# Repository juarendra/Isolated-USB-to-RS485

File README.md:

# Industrial USB to RS485 Adapter

USB Type-C to isolated half-duplex RS485 interface for Modbus RTU and other UART-based industrial networks.

## Product Summary

This board converts a USB serial connection into an electrically isolated RS485 bus. It is suitable for connecting a computer, single-board computer, or industrial controller to RS485/Modbus RTU equipment.

```text
USB Type-C -> FT231XS UART -> ADuM1201 isolation -> MAX485 -> RS485 A/B
```

The design files are provided for evaluation, manufacturing, and integration. Read the limitations and validation notes before using the board in a safety-critical or compliance-regulated product.

## Features

- USB Type-C USB 2.0 connection
- FTDI FT231XS USB-to-UART bridge
- 3.3 V UART I/O configuration
- Isolated UART data path using ADuM1201ARZ
- Isolated 5 V supply using IL0505S
- MAX485 half-duplex RS485 transceiver
- RS485 A, B, and isolated ground connector
- Selectable RS485 termination and bias networks
- RS485 transient protection using SM712, TBU, and TISP devices
- TX, RX, and power status indicators
- Resettable USB input protection
- Separate isolated 5 V output connector
- Eagle schematic, board, libraries, Gerber archive, 3D model, and enclosure files

## Quick Start

1. Connect the board to a host computer using a USB Type-C data cable.
2. Install the FTDI VCP driver if the operating system does not install it automatically.
3. Identify the new serial port.
4. Connect RS485 `A`, `B`, and optionally `GNDA` to the target equipment.
5. Configure the host application for the target baud rate, parity, stop bits, and protocol.
6. Enable termination only when this adapter is at a physical end of the RS485 bus.
7. Enable bias only when this adapter is the designated bias point for the bus.

## Connector Pinout

See the visual pinout: [`DOC/HARDWARE/Pinout.png`](DOC/HARDWARE/Pinout.png).

| Connector | Pin | Function |
|---|---:|---|
| RS485 | 1 | `GNDA` / isolated ground |
| RS485 | 2 | `B` |
| RS485 | 3 | `A` |
| POWER | 1 | `GNDA` |
| POWER | 2 | `VCC`, isolated 5 V |
| POWER | 3 | `VCC`, isolated 5 V |

Confirm connector orientation against the silkscreen and pinout image before wiring.

## Design Files

| Resource | Location |
|---|---|
| Schematic PDF | [`PDF/Schematic.pdf`](PDF/Schematic.pdf) |
| Eagle schematic | [`PCB-EAGLE/IndustrialUSBtoModbus.sch`](PCB-EAGLE/IndustrialUSBtoModbus.sch) |
| Eagle board | [`PCB-EAGLE/IndustrialUSBtoModbus.brd`](PCB-EAGLE/IndustrialUSBtoModbus.brd) |
| Manufacturing Gerbers | [`CAD-CAM/Gerber.zip`](CAD-CAM/Gerber.zip) |
| Production PCB | [`PCB-EAGLE/IndustrialUSBtoModbus_Production.brd`](PCB-EAGLE/IndustrialUSBtoModbus_Production.brd) |
| Production Gerbers | [`CAD-CAM/Gerber_Production.zip`](CAD-CAM/Gerber_Production.zip) |
| Production CAM job | [`CAD-CAM/IndustrialUSBtoModbus v2.cam`](CAD-CAM/IndustrialUSBtoModbus%20v2.cam) |
| Board dimensions | [`DOC/Dimension.pdf`](DOC/Dimension.pdf) |
| STEP model | [`3D/IndustrialUSBtoModbus.step`](3D/IndustrialUSBtoModbus.step) |
| Enclosure models | [`3D/Case/`](3D/Case/) |
| Custom Eagle libraries | [`PCB-EAGLE/lib/`](PCB-EAGLE/lib/) |

Detailed documentation is in [`docs/`](docs/).

For manufacturing, use the files marked **Production**. The production Gerber archive contains Gerber, drill, solder-paste, pick-and-place, job, and ODB++ outputs generated from the production PCB revision.

## Important Limitations

- This is a half-duplex RS485 hardware interface; it does not implement Modbus protocol in hardware.
- RS485 termination, bias values, isolation spacing, and protection ratings require system-level verification.
- Cable length, baud rate, node count, and bus topology depend on the transceiver, cable, and installation.
- Custom FTDI VID/PID programming requires valid ownership/licensing and separate production configuration.

## Buyer Information

Before purchasing or manufacturing, review:

- [`docs/BUYER-GUIDE.md`](docs/BUYER-GUIDE.md) for compatibility and ordering checks
- [`docs/HARDWARE.md`](docs/HARDWARE.md) for circuit behavior and configuration
- [`docs/VALIDATION.md`](docs/VALIDATION.md) for required production tests
- [`docs/FTDI-PROGRAMMING.md`](docs/FTDI-PROGRAMMING.md) for FT231XS production programming
- [`docs/FILES.md`](docs/FILES.md) for the complete repository map

## License

No license is currently declared. Contact the repository owner for permission to manufacture, modify, or redistribute this design.

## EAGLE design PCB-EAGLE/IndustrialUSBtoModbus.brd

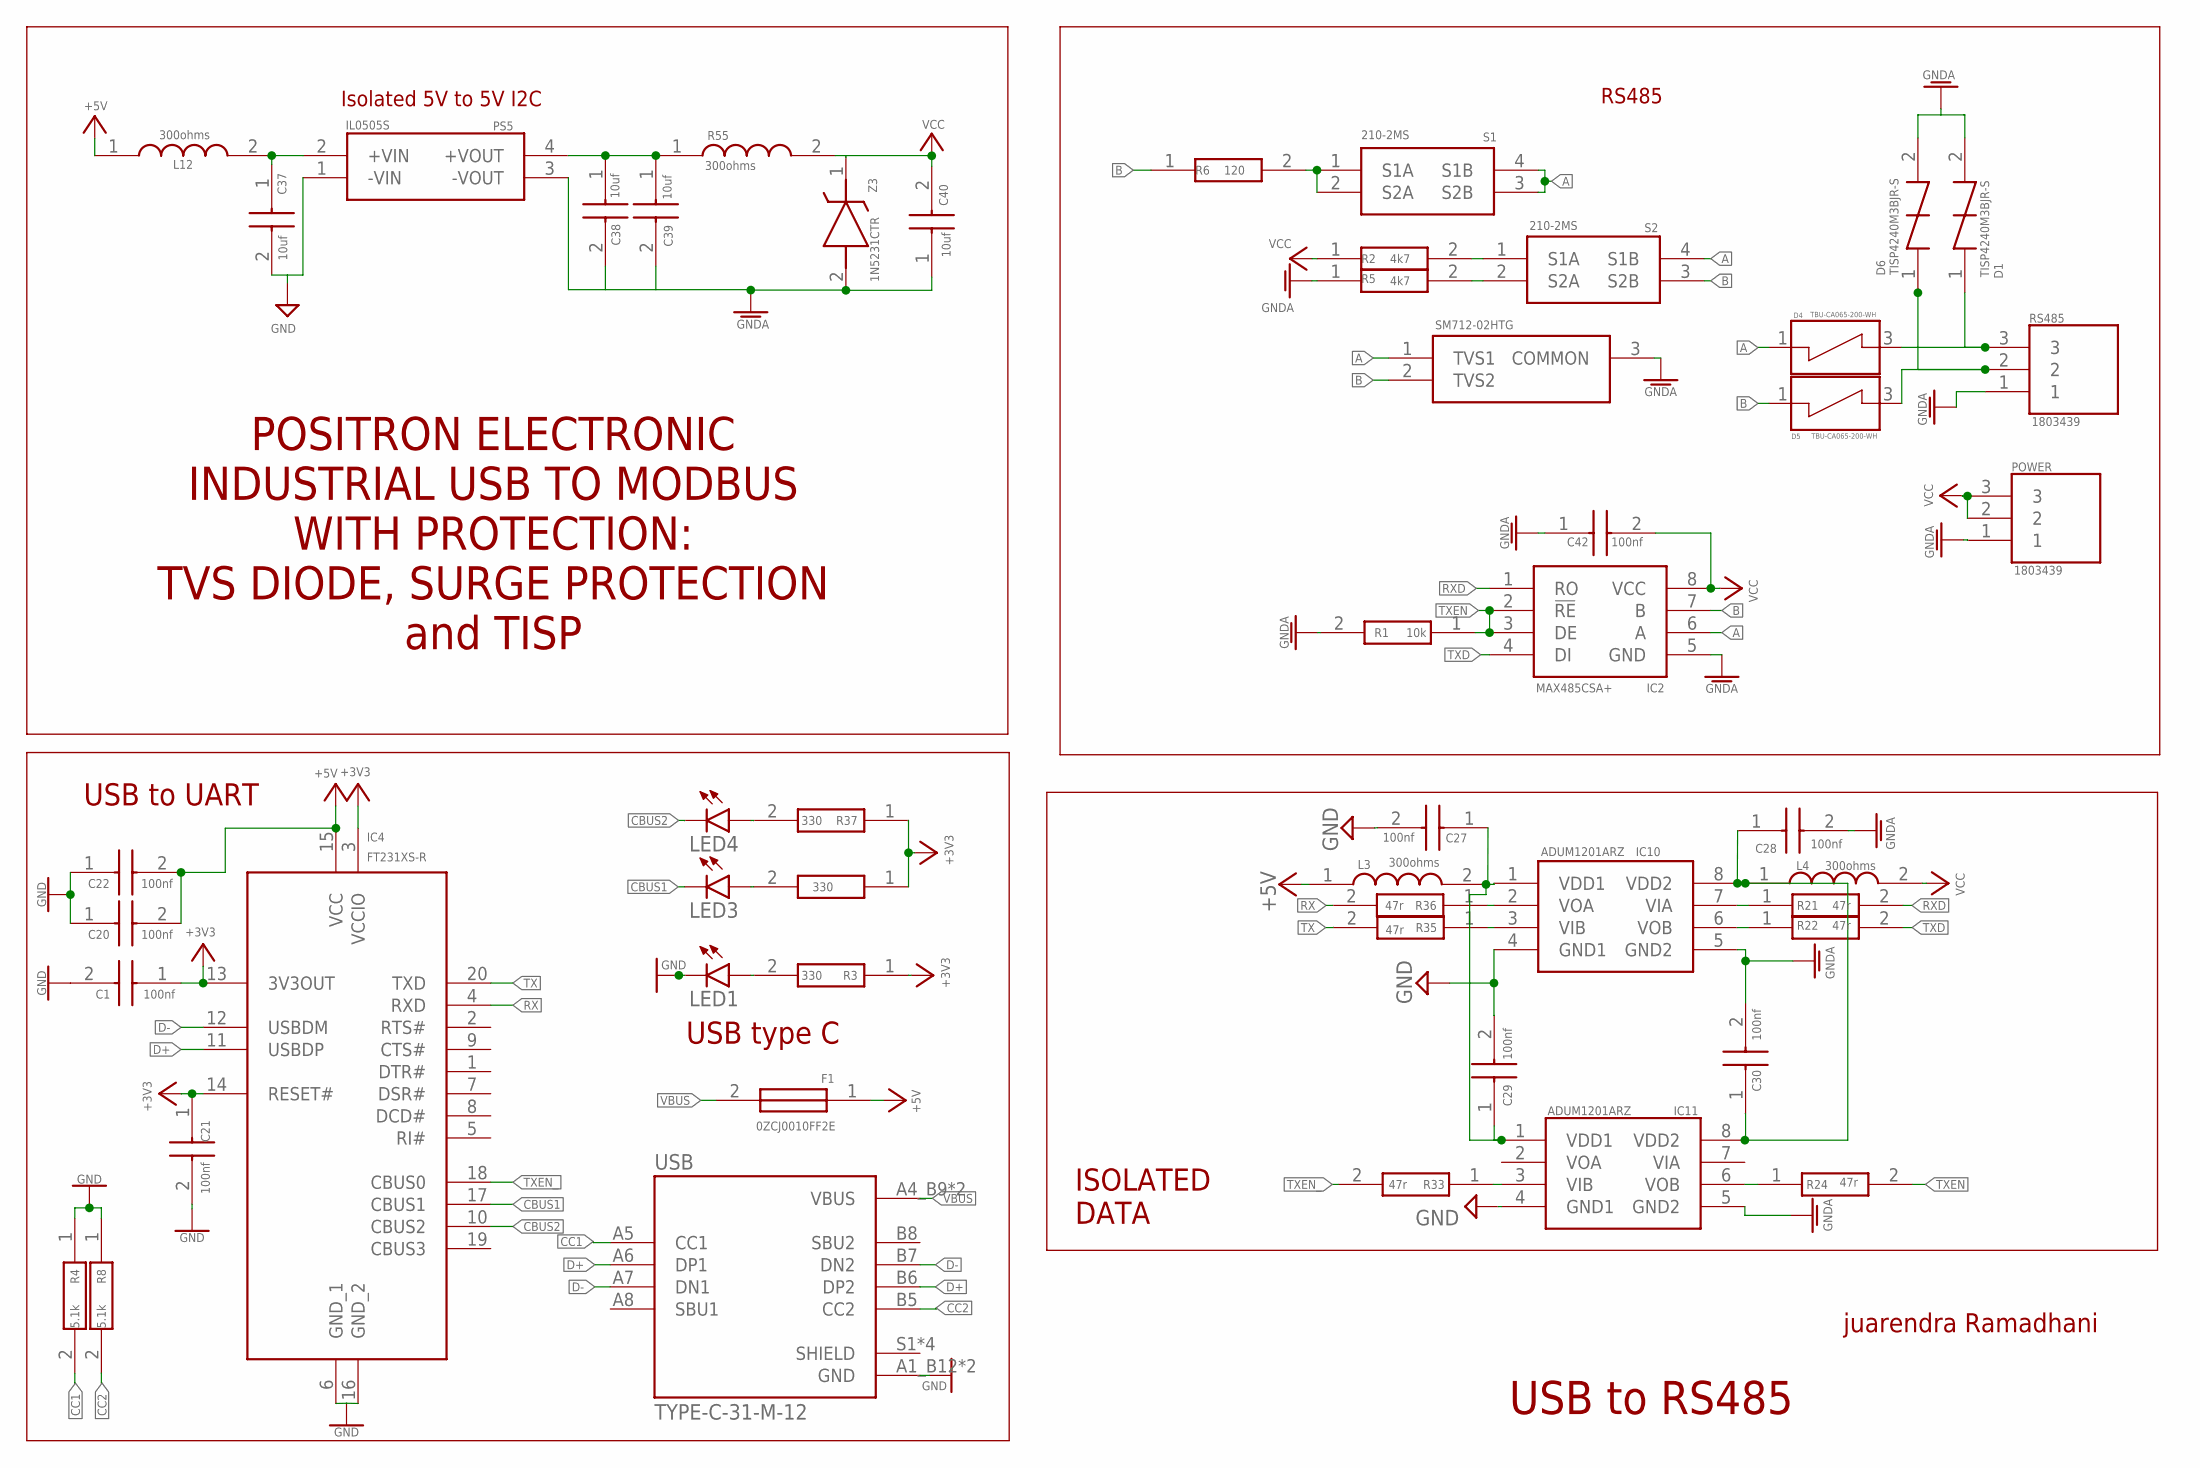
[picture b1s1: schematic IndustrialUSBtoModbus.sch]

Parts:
C1, C20, C21, C22, C27, C28, C29, C30, C42: 100nf; CAPC1608X87N
C37, C38, C39, C40: 10uf; CAPC3216X170N
D1, D6: TISP4240M3BJR-S; TISP4240M3BJRS
D2: SM712-02HTG; SOT95P237X111-3N
D4, D5: TBU-CA065-200-WH; DIOC650X400X100N
F1: 0ZCJ0010FF2E; FUSC3216X75N
IC2: MAX485CSA+; SOIC127P600X175-8N
IC4: FT231XS-R; SOP64P599X175-20N
IC10, IC11: ADUM1201ARZ; SOIC127P600X175-8N
L3, L4, L12: 300ohms; INDC1608X95N
LED1, LED3, LED4: LED3MM
POWER: 1803439
PS5: IL0505S
R1: 10k; ERJ3EK_(0603)
R2, R5: 4k7; RESC2012X65N
R3, R37, R38: 330; ERJH3
R4, R8: 5.1k; ERJH3
R6: 120; RESC2012X65N
R21, R22, R24, R33, R35, R36: 47r; RESC1608X55N
R55: 300ohms; INDC1608X95N
RS485: 1803439
S1, S2: 210-2MS; DIP775W63P254L655H458Q4N
USB: TYPE-C-31-M-12; HRO_TYPE-C-31-M-12
Z3: 1N5231CTR; DIOAD1068W53L380D172

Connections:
+3V3: C1.1, C21.1, IC4.3 (VCCIO), IC4.13 (3V3OUT), IC4.14 (RESET#), R3.1, R37.1, R38.1
+5V: C20.2, C22.2, F1.1, IC4.15 (VCC), L3.1, L12.1
A: D2.1 (TVS1), D4.1, IC2.6 (A), S1.3 (S2B), S1.4 (S1B), S2.4 (S1B)
B: D2.2 (TVS2), D5.1, IC2.7 (B), R6.1, S2.3 (S2B)
CBUS1: IC4.17 (CBUS1), LED3.K (C)
CBUS2: IC4.10 (CBUS2), LED4.K (C)
CC1: R4.2, USB.A5 (CC1)
CC2: R8.2, USB.B5 (CC2)
D+: IC4.11 (USBDP), USB.A6 (DP1), USB.B6 (DP2)
D-: IC4.12 (USBDM), USB.A7 (DN1), USB.B7 (DN2)
GND: C1.2, C20.1, C21.2, C22.1, C27.2, C29.2, C37.2, IC4.6 (GND_1), IC4.16 (GND_2), IC10.4 (GND1), IC11.4 (GND1), LED1.K (C), PS5.1 (-VIN), R4.1, R8.1, USB.A1_B12 (GND), USB.B1_A12 (GND)
GNDA: C28.2, C30.2, C38.2, C39.2, C40.1, C42.1, D1.2, D2.3 (COMMON), D6.2, IC2.5 (GND), IC10.5 (GND2), IC11.5 (GND2), POWER.1, PS5.3 (-VOUT), R1.2, R5.1, RS485.1, Z3.2 (A)
unnamed: C28.1, C30.1, IC10.8 (VDD2), IC11.8 (VDD2), L4.1
unnamed: IC10.6 (VOB), R22.1
unnamed: LED3.A, R38.2
unnamed: IC10.7 (VIA), R21.1
unnamed: R2.2, S2.1 (S1A)
unnamed: R5.2, S2.2 (S2A)
unnamed: D5.3, D6.1, RS485.2
unnamed: LED1.A, R3.2
unnamed: D1.1, D4.3, RS485.3
unnamed: R6.2, S1.1 (S1A), S1.2 (S2A)
unnamed: LED4.A, R37.2
unnamed: C27.1, C29.1, IC10.1 (VDD1), IC11.1 (VDD1), L3.2
unnamed: IC10.3 (VIB), R35.1
unnamed: IC10.2 (VOA), R36.1
unnamed: IC11.6 (VOB), R24.1
unnamed: IC11.3 (VIB), R33.1
unnamed: C37.1, L12.2, PS5.2 (+VIN)
unnamed: C38.1, C39.1, PS5.4 (+VOUT), R55.1
RX: IC4.4 (RXD), R36.2
RXD: IC2.1 (RO), R21.2
TX: IC4.20 (TXD), R35.2
TXD: IC2.4 (DI), R22.2
TXEN: IC2.2 (!RE), IC2.3 (DE), R1.1, R24.2
TXEN_: IC4.18 (CBUS0), R33.2
VBUS: F1.2, USB.A4_B9 (VBUS), USB.B4_A9 (VBUS)
VCC: C40.2, C42.2, IC2.8 (VCC), L4.2, POWER.2, POWER.3, R2.1, R55.2, Z3.1 (K)

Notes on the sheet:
USB to UART
USB type C
USB to RS485
juarendra Ramadhani
RS485
Isolated 5V to 5V I2C
ISOLATED DATA
POSITRON ELECTRONIC INDUSTRIAL USB TO MODBUS WITH PROTECTION: TVS DIODE, SURGE PROTECTION and TISP

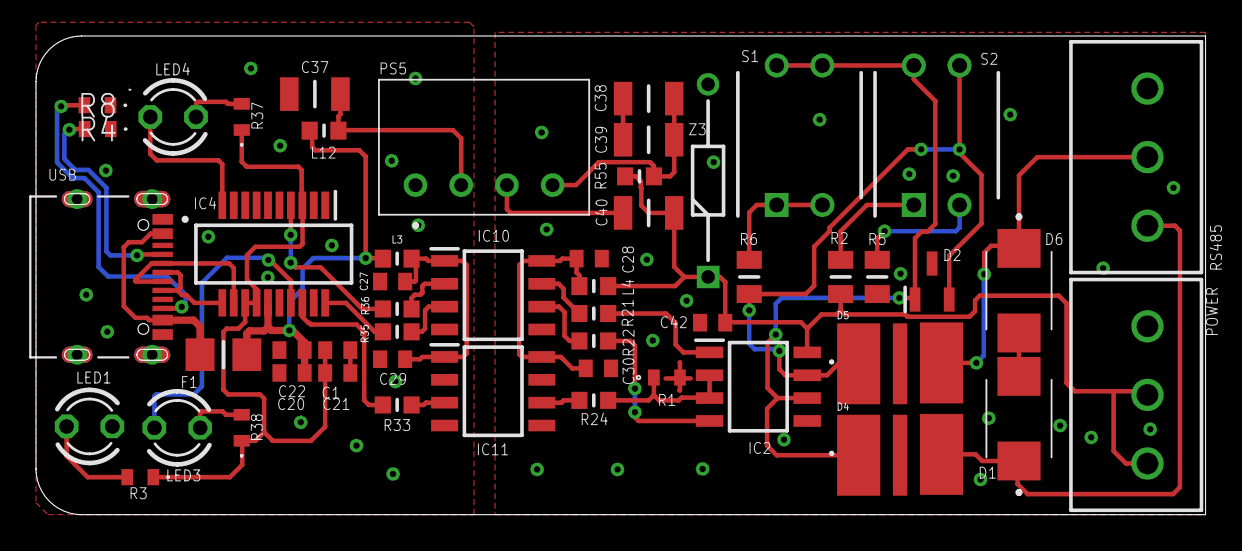
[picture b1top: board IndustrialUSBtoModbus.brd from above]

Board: 2 copper layers, 65.0 x 26.6 mm, 52 parts (0 on the bottom side), 38 nets.
